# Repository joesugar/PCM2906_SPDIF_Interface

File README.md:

# PCM2906_SPDIF_Interface
Eagle CAD files for a PCM2906 SPDIF interface card.

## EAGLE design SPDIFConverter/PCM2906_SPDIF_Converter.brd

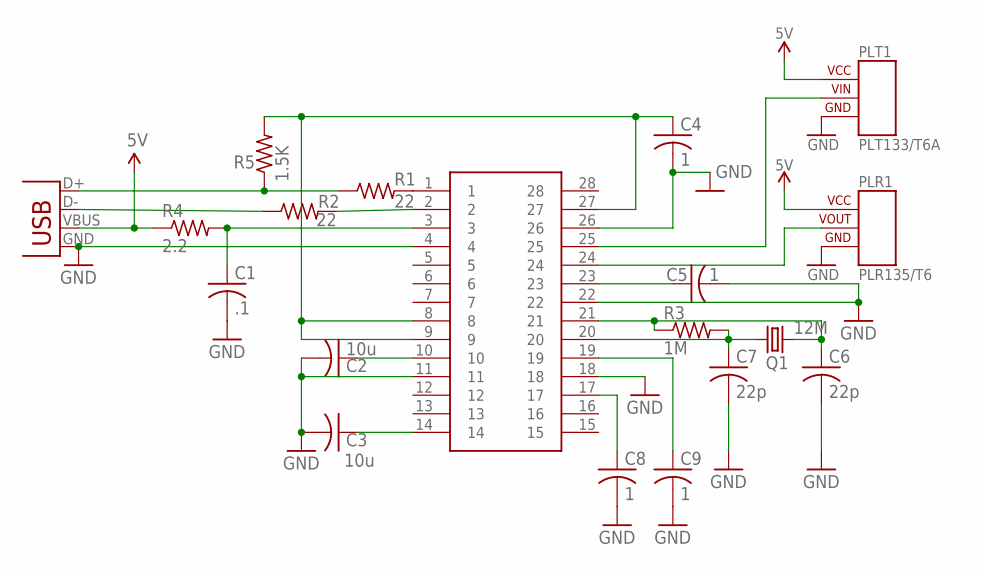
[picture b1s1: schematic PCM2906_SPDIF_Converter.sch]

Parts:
C1: .1; C0805
C2, C3: 10u; C1210
C4, C5, C8, C9: 1; C1210
C6, C7: 22p; C0805
PCM2906: SSOP28; SSOP28DB
PLR1: PLR135/T6
PLT1: PLT133/T6A
Q1: 12M; HC49US
R1, R2: 22; R0805
R3: 1M; R0805
R4: 2.2; R0805
R5: 1.5K; R0805
X2: USBSMD; USB-MINIB

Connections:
5V: PLR1.VCC, PLT1.VCC, R4.1, X2.VBUS
GND: C1.2, C2.2, C3.2, C4.2, C5.2, C6.2, C7.2, C8.2, C9.2, PCM2906.4, PCM2906.11, PCM2906.18, PCM2906.22, PCM2906.26, PLR1.GND, PLT1.GND, X2.GND
unnamed: PCM2906.1, R1.2
unnamed: PCM2906.2, R2.2
unnamed: C6.1, PCM2906.21, Q1.2, R3.1
unnamed: R1.1, R5.1, X2.D+
unnamed: R2.1, X2.D-
unnamed: PCM2906.24, PLR1.VOUT
unnamed: C4.1, PCM2906.8, PCM2906.9, PCM2906.27, R5.2
unnamed: C5.1, PCM2906.23
unnamed: C2.1, PCM2906.10
unnamed: C3.1, PCM2906.14
unnamed: C1.1, PCM2906.3, R4.2
unnamed: PCM2906.25, PLT1.VIN
unnamed: C8.1, PCM2906.17
unnamed: C9.1, PCM2906.19
unnamed: C7.1, PCM2906.20, Q1.1, R3.2

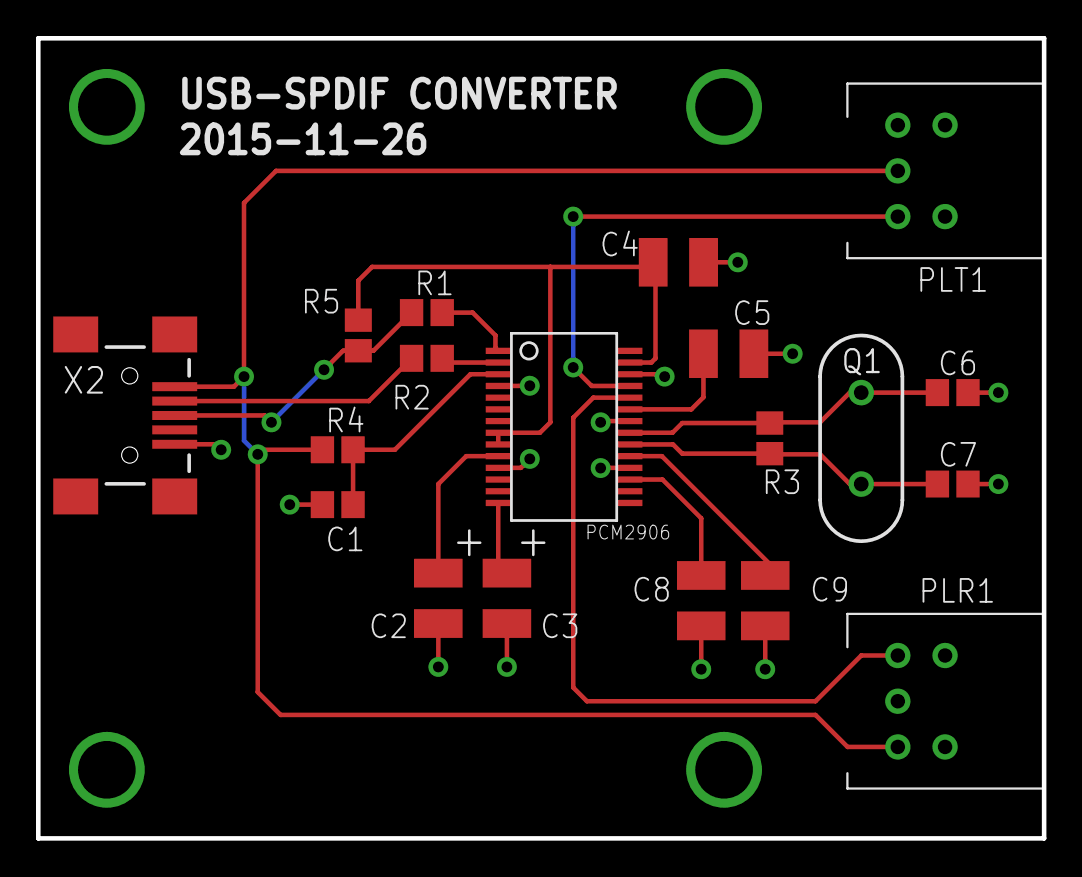
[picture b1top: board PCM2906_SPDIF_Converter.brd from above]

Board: 2 copper layers, 55.9 x 44.5 mm, 19 parts (0 on the bottom side), 17 nets.

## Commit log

2016-02-15 Initial commit of converter board.

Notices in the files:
parts and their libraries:
SparkFun-Aesthetics: Licensing: Creative Commons ShareAlike 4.0 International - https://creativecommons.org/licenses/by-sa/4.0
